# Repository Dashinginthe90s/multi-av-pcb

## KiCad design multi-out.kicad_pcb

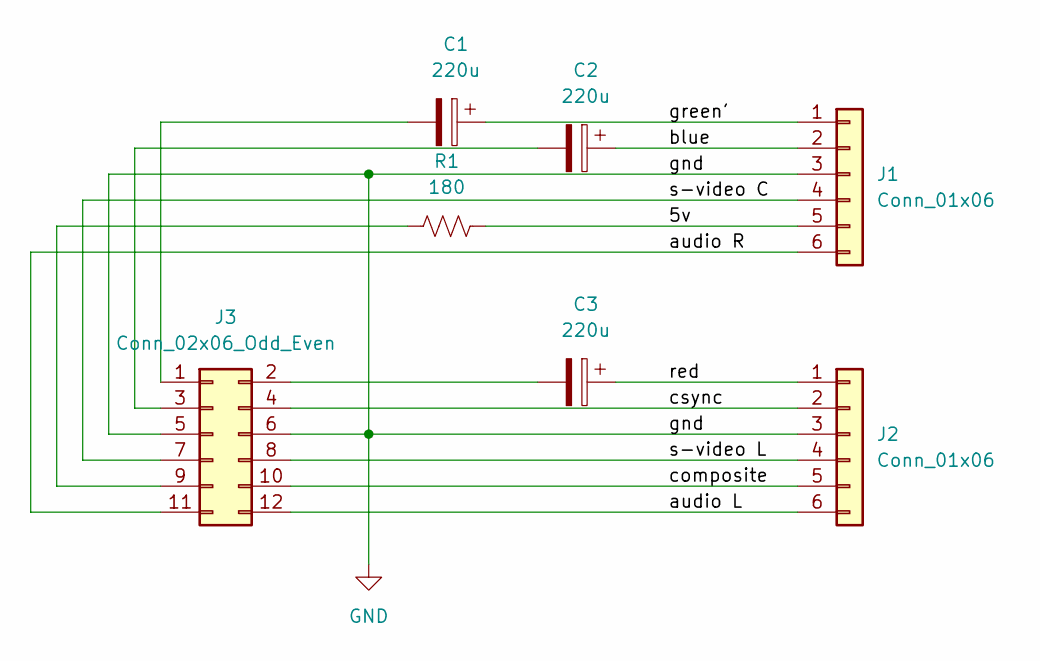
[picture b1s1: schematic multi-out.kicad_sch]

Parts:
C1, C2, C3: 220u; C_0603_1608Metric_Pad1.08x0.95mm_HandSolder
J1, J2: Conn_01x06; nintendo multi av
J3: Conn_02x06_Odd_Even; PinHeader_2x06_P2.54mm_Vertical
R1: 180; R_0603_1608Metric_Pad0.98x0.95mm_HandSolder

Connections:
/5v: J1.5, R1.2
/audio L: J2.6, J3.12
/audio R: J1.6, J3.11
/blue: C2.1, J1.2
/composite: J2.5, J3.10
/csync: J2.2, J3.4
/green': C1.1, J1.1
/red: C3.1, J2.1
/s-video C: J1.4, J3.7
/s-video L: J2.4, J3.8
GND: J1.3, J2.3, J3.5, J3.6
unnamed: C1.2, J3.1
unnamed: C2.2, J3.3
unnamed: C3.2, J3.2
unnamed: J3.9, R1.1

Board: 2 copper layers, 7 parts (4 on the bottom side), 15 nets, no tracks yet.

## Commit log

2022-06-28 inital commit
